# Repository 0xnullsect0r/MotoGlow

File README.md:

# MotoGlow

Addressable accent lighting for a 2023 KTM 890 Adventure. Sixteen animated
presets, all flowing front to rear, on a Raspberry Pi Pico 2 W driving four runs
of 12 V addressable COB strip, in a printed enclosure you can hose off.

Everything here is built and checked, not sketched: the firmware compiles clean
for the RP2350, the CAD renders to manifold STLs, and the PCB passes
connectivity, clearance, edge and ground-pour checks.

```
firmware/motoglow/   Arduino / FastLED firmware for the Pico 2 W
cad/                 Parametric OpenSCAD enclosure, saddle, strip clips, end caps
hardware/motoglow-pcb/  KiCad board, generated + routed + verified by script
docs/                Parts list, wiring, build guide, bike map, presets
tools/               Host test for the direction invariant
```

Start with [docs/PARTS.md](docs/PARTS.md), then
[docs/BUILD.md](docs/BUILD.md).

**[Preset bench](https://claude.ai/artifact/BSTM89HNMauqSr1nQH6gRN)** — all sixteen
presets running live on a side elevation of the bike, at the coordinates the
firmware actually uses, with the firmware's own current estimator reporting what
each one draws. A local copy is at `docs/preset-bench.html`.

---

## The one idea worth reading about

Almost every DIY strip controller animates against the LED index — pixel 0,
then 1, then 2. That works on a bench and falls apart on a motorcycle, because
the LEDs are not in a line. A run goes up a fork leg, jumps a metre of air to
the tank, runs level along the seat, then drops onto a swingarm. An index sweep
crawls up the fork, teleports across the gap, then races down the seat. It reads
as four separate strips blinking in sequence.

MotoGlow gives every pixel a physical position on the bike and renders effects
as a function of **position and time**:

```c
x      0.0 = front axle    1.0 = rear axle     (1509 mm on this bike)
y      0.0 = ground        1.0 = 1350 mm up
side  -1 left    0 centre    +1 right
```

A block moving at 0.38 bike-lengths per second moves at that speed across the
*bike*. It takes the right amount of time to cross the fork, is absent for
exactly as long as the gap is wide, and reappears on the tank where it should.
Your eye joins it up, and the whole bike reads as one object rather than as
several strips.

The consequences are practical. You can rewire a run backwards, shorten a
segment, or add one, and only a table in `bike_map.cpp` changes. Rainbows,
comets, gradients and wipes are three lines of maths each. And "always flows
front to rear" is structural rather than a convention: the two phase helpers in
`phase.h` are the only way any effect can express position, and they only run
one way. There is a host test that proves it, including after 99,999 seconds of
runtime, where float precision starts to bite.

---

## What's in the box

**Firmware.** 16 presets over 8 motion primitives, 400 ms crossfades, a
two-sweep-then-bloom power-on sequence, and per-frame current estimation derived
from the strip's datasheet figures rather than guessed. Settings survive power
cycles, with flash writes deferred 5 seconds so clicking through ten presets
costs one erase. Battery protection is staged — the strips visibly back off and
breathe before the pack gets low enough to strand you — because this is a
battery-direct install with no ignition interlock.

**Electronics.** A P-channel MOSFET master switch means the handlebar toggle
carries about 110 µA instead of 3 A, and that the box draws exactly nothing when
it's off. A 74AHCT125 buffers all four data lines to 5 V, which is the single
most common reason home-built strip controllers glitch: the strips want 3.5 V on
data and a Pico puts out 3.3 V — fine on a bench, unreliable on three feet of
wire next to an ignition system. Reverse polarity is cleared by a TVS blowing
the fuse, so **the fuse is a functional part of the circuit, not a formality.**

**Enclosure.** Parametric, because the PCB size will change at least twice
before you're done. The gasket groove sits inboard of the lid screws, so a screw
hole that takes on water is still outside the seal, and nothing penetrates the
floor — the frame-tube saddle is a separate part for exactly that reason.

---

## Honest limitations

- The bike-space coordinates are my reading of an 890 Adventure's proportions,
  not measurements of your bike. They'll look fine as shipped and better after
  ten minutes with a tape measure — see [docs/BIKE_MAP.md](docs/BIKE_MAP.md).
- Nothing here has been built in the physical world. Every check that can be run
  in software has been; none of it has been run on a bike.
- The box is 115 × 110 × 43 mm. It is bigger than the first revision because
  panel connectors need real space inboard of the wall, which that revision
  did not give them.
- IP65–66 realistically, not IP68. Rain, spray and a hose are fine. A pressure
  washer lance is not, whatever anyone claims about FDM parts.
- There's no brake or turn-signal integration, by choice. Strip runs and the
  loom are simpler for it.
- This is show lighting. Underglow that's on while moving is restricted or
  banned in a good number of US states, and red or blue visible from the front
  is a criminal matter rather than a ticket in some of them. The toggle is the
  compliance mechanism.

---

## Verification

| | |
|---|---|
| Firmware | Compiles clean for `rp2040:rp2040:rpipico2w` at `--warnings all`; 8% flash, 14% RAM |
| Direction invariant | 18 host assertions pass (`g++ -o /tmp/t tools/test_phase.cpp && /tmp/t`) |
| Enclosure | All 5 STLs render 2-manifold; dimensions checked against the parameters |
| PCB | 0 unconnected nets, 0 clearance violations below 0.25 mm, 0 items within 0.3 mm of the outline, 0 silkscreen over pads, ground pour is a single region reaching all 35 ground pads |
| Case ↔ PCB | `verify_fit.py`: board fits, posts land on the real holes, 0 connector/component collisions, 0 keep-out violations |
| Part pinouts | IRF4905, R-78E5.0, 74AHCT125, Pico row pitch and all three diode footprints checked against datasheets, not memory |
| Fab output | 128 plated drill hits + 4 NPTH at 2.7 mm, matching the design exactly |

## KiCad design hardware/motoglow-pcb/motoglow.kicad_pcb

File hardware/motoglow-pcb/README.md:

# MotoGlow controller PCB

Two layers, 80 × 60 mm, every part through-hole so it can be hand-assembled.
All signal routing is on the top layer; the bottom is an uninterrupted ground
pour. The board uses zero vias, which is a happy accident of that split and
means nothing to go wrong in plating.

## Ordering it

Upload `motoglow-gerbers.zip` to any fab. Defaults are fine: 2 layers, 1.6 mm,
1 oz copper, HASL or ENIG, any colour. Nothing on the board is near a process
limit — the tightest trace is 0.3 mm, the tightest clearance 0.25 mm, and the
smallest drill 0.8 mm.

No assembly service is needed or wanted: the whole point of an all-through-hole
board is that you solder it yourself in an evening.

## Regenerating

```
python3 gen_pico_fp.py      # writes lib.pretty/RPi_Pico_2W_Horizontal.kicad_mod
python3 route.py            # export DSN -> freerouting -> import SES -> pour
python3 verify_board.py     # connectivity, clearance, edge, pour, silkscreen
python3 verify_fit.py       # does the enclosure fit this board?
python3 export_pcb_data.py  # hand the board's real dimensions to the CAD
```

`mech.py` holds every number that couples the board to the enclosure, and both
sides read it. `../../cad/build.sh` runs the exporter and the fit check before
it renders anything, so a board change that breaks the case stops the build
rather than the print.

`route.py` needs `freerouting.jar` (set `FREEROUTING_JAR`) and runs it under
`xvfb-run`, because freerouting insists on a display even in batch mode.

`motoglow.ses` is committed deliberately. Freerouting does not guarantee a
identical result between runs, so keeping the session file means the board in
`motoglow.kicad_pcb` can be reproduced exactly rather than approximately.

## Why the checks are hand-written

KiCad 7's command line has no `pcb drc` subcommand — that arrived in KiCad 8 —
so `verify_board.py` does the job geometrically. It checks four things:

- **Connectivity.** Every pad of every routed net lands in one connected group
  of copper. This is what catches a coordinate sign or scale error in the SES
  import, which otherwise produces a board that looks entirely plausible and is
  wired to nothing.
- **Clearance.** No two pieces of copper on different nets come closer than
  0.25 mm. Pads are modelled by their true shape; a rectangular pad treated as
  a circle through its corners over-states it by 0.35 mm on a 1.7 mm pad and
  invents violations that are not there.
- **Board edge.** Nothing within 0.3 mm of the outline.
- **Ground pour.** The pour is a single region, and every ground pad reaches it
  through at least two thermal spokes. A pad sitting inside its relief with no
  spoke bridging to the pour looks perfect on screen and is not connected.

`verify_fit.py` is the fifth check, and the one this project learned the hard
way. Revision A shipped a case built for a 75 x 55 mm board that had since
become 80 x 60, with all six connector bodies landing inside components. Both
halves passed their own checks perfectly; nothing compared them. It also has a
negative test: forcing revision A's geometry back in makes it report all 19
collisions.

Current state: **0 unconnected nets, 0 clearance violations, 0 edge violations,
0 silkscreen over pads, pour is 1 region with all 35 ground pads connected,
0 connector/component collisions.**

## Two things worth knowing before you power it

**The fuse is not optional.** Reverse polarity protection here is D2, a
unidirectional TVS across the input. Connect the battery backwards and D2
conducts, which is only a protection strategy if there is a fuse for it to
blow. Without one, D2 becomes the fuse, once.

**Tall parts live in the middle of the board.** Anything standing within 14 mm
of an edge shares that space with a panel connector's barrel, so `mech.py` caps
it at 11 mm — the height of the screw terminals, which genuinely have to be on
the edge. That is why Q1, C1 and D2 are in the middle rather than tucked
tidily against a wall. `verify_fit.py` enforces it.

**Q1 is the master switch and the handlebar toggle barely touches it.** Q1 is a
P-channel MOSFET with its source on the battery; the toggle pulls its gate down
through R2 and draws about 110 µA doing it. So the switch wiring is signal wire,
not power wire, and with the toggle open the board's draw is zero rather than
small — which matters on a battery-direct install that may sit for a month.

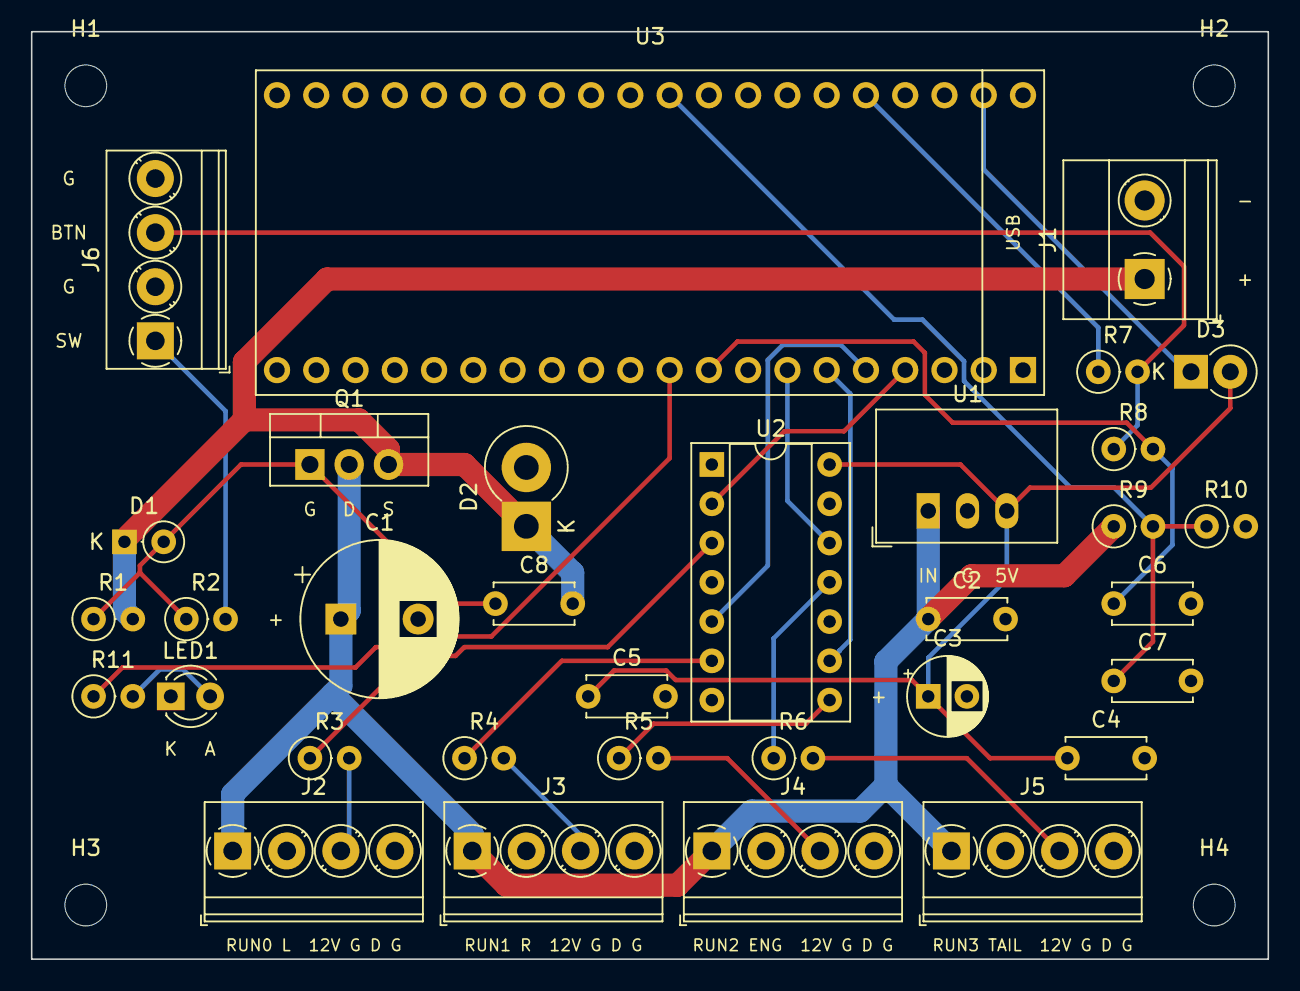
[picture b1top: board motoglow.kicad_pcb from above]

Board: 2 copper layers, 80.0 x 60.0 mm, 37 parts (0 on the bottom side), 25 nets.

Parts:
C1: 470uF 35V; CP_Radial_D10.0mm_P5.00mm
C2, C4, C5, C6, C7, C8: 100nF; C_Disc_D5.0mm_W2.5mm_P5.00mm
C3: 10uF 16V; CP_Radial_D5.0mm_P2.50mm
D1: BZX55C15; D_DO-35_SOD27_P2.54mm_Vertical_KathodeUp
D2: 1.5KE18A; D_DO-201AD_P3.81mm_Vertical_KathodeUp
D3: 1N5819; D_DO-41_SOD81_P2.54mm_Vertical_KathodeUp
H1, H2, H3, H4: M2.5; MountingHole_2.7mm_M2.5
J1: 12V IN; TerminalBlock_Phoenix_MKDS-1,5-2-5.08_1x02_P5.08mm_Horizont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
J2: RUN0 L; TerminalBlock_Phoenix_PT-1,5-4-3.5-H_1x04_P3.50mm_Horizontal
J3: RUN1 R; TerminalBlock_Phoenix_PT-1,5-4-3.5-H_1x04_P3.50mm_Horizontal
J4: RUN2 ENG; TerminalBlock_Phoenix_PT-1,5-4-3.5-H_1x04_P3.50mm_Horizontal
J5: RUN3 TAIL; TerminalBlock_Phoenix_PT-1,5-4-3.5-H_1x04_P3.50mm_Horizontal
J6: BAR; TerminalBlock_Phoenix_PT-1,5-4-3.5-H_1x04_P3.50mm_Horizontal
LED1: STATUS; LED_D3.0mm
Q1: IRF4905; TO-220-3_Vertical
R1: 100k; R_Axial_DIN0207_L6.3mm_D2.5mm_P2.54mm_Vertical
R2, R7, R10: 10k; R_Axial_DIN0207_L6.3mm_D2.5mm_P2.54mm_Vertical
R3, R4, R5, R6: 330; R_Axial_DIN0207_L6.3mm_D2.5mm_P2.54mm_Vertical
R8: 1k; R_Axial_DIN0207_L6.3mm_D2.5mm_P2.54mm_Vertical
R9: 47k; R_Axial_DIN0207_L6.3mm_D2.5mm_P2.54mm_Vertical
R11: 470; R_Axial_DIN0207_L6.3mm_D2.5mm_P2.54mm_Vertical
U1: R-78E5.0-1.0; Converter_DCDC_RECOM_R-78E-0.5_THT
U2: 74AHCT125N; DIP-14_W7.62mm_Socket
U3: Pico 2 W; RPi_Pico_2W_Horizontal

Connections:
+3V3: R7.1, U3.36
+5V: C3.1, C4.1, C5.1, D3.2, U1.3, U2.14
+12VSW: C1.1, C2.1, J2.1, J3.1, J4.1, J5.1, Q1.2, R9.1, U1.1
BAT+: C8.2, D1.1, D2.1, J1.1, Q1.3, R1.2
BTN: J6.3, R7.2, R8.1
DATA0: J2.3, R3.2
DATA1: J3.3, R4.2
DATA2: J4.3, R5.2
DATA3: J5.3, R6.2
GATE: C8.1, D1.2, Q1.1, R1.1, R2.1
GND: C1.2, C2.2, C3.2, C4.2, C5.2, C6.2, C7.2, D2.2, J1.2, J2.2, J2.4, J3.2, J3.4, J4.2, J4.4, J5.2, J5.4, J6.2, J6.4, LED1.1, R10.2, U1.2, U2.1, U2.4, U2.7, U2.10, U2.13, U3.3, U3.8, U3.13, U3.18, U3.23, U3.28, U3.33, U3.38
GP2: U2.2, U3.4
GP3: U2.5, U3.5
GP4: U2.9, U3.6
GP5: U2.12, U3.7
GP6: C6.1, R8.2, U3.9
GP7: R11.1, U3.10
LED_A: LED1.2, R11.2
SW_A: J6.1, R2.2
VSENSE: C7.1, R9.2, R10.1, U3.31
VSYS: D3.1, U3.39
Y1: R3.1, U2.3
Y2: R4.1, U2.6
Y3: R5.1, U2.8
Y4: R6.1, U2.11
